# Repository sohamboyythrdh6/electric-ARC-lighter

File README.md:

# electric-ARC-lighter
an electric lighter is a very useful project. which can be use for start a fire or ignite our gas stove .it's not like other lighters because it is charge by a type c charger and it dosen't need to refill gas .just charge and whenever need just press the switch and use.this project will teach us how crazy and dangerous can a hihg voltage transformer is which can turn 5 volt into 1000 of volts.

to build this lighter you jest need to collect the components pcb and those 3d models then connect all the parts to the pcb using solder later confirming everypart is in correct place put everything in the case and glued it and then it will be ready to use .But before using full charge this.

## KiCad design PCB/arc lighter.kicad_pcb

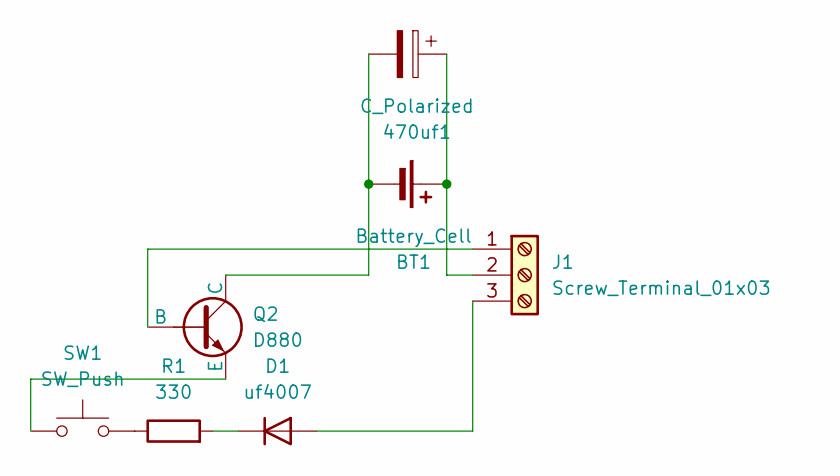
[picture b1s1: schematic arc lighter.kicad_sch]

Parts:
470uf1: C_Polarized; CP_Radial_D7.5mm_P2.50mm
BT1: Battery_Cell; PinSocket_1x02_P2.00mm_Vertical
D1: uf4007; D_A-405_P7.62mm_Horizontal
J1: Screw_Terminal_01x03; TerminalBlock_MaiXu_MX126-5.0-03P_1x03_P5.00mm
Q2: D880; TO-220-3_Horizontal_TabDown
R1: 330; R_Axial_DIN0204_L3.6mm_D1.6mm_P5.08mm_Horizontal
SW1: SW_Push; SW_PUSH-12mm

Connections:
unnamed: 470uf1.1, BT1.1 (+), J1.2
unnamed: 470uf1.2, BT1.2 (-), Q2.1 (C)
unnamed: D1.2 (A), J1.3
unnamed: D1.1 (K), R1.2
unnamed: J1.1, Q2.2 (B)
unnamed: Q2.3 (E), SW1.1
unnamed: R1.1, SW1.2

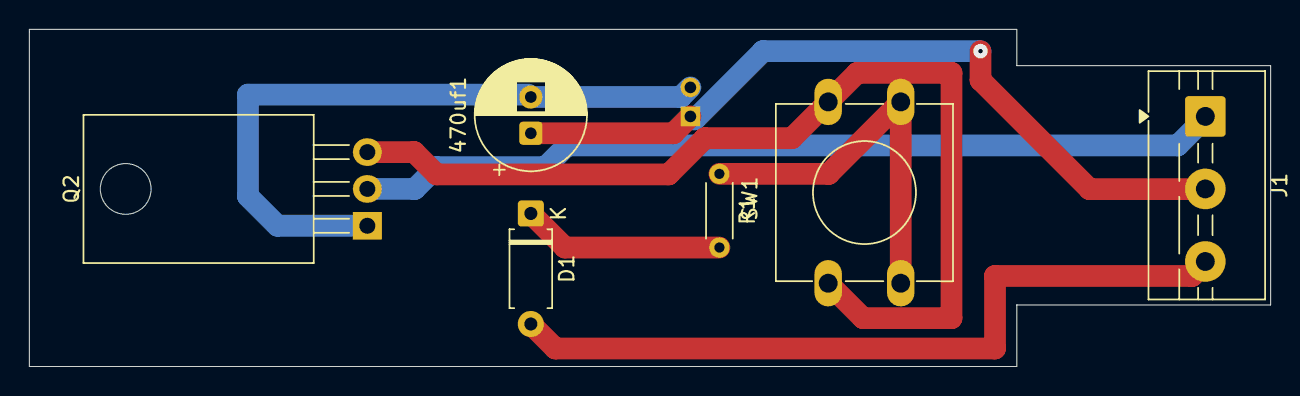
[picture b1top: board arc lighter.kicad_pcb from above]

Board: 2 copper layers, 85.6 x 23.2 mm, 7 parts (1 on the bottom side), 7 nets.

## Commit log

2026-05-15 Create ;
2026-05-15 Create 6
2026-06-01 Create 2
2026-06-01 Rename New folder.rar to Gerber.zip
